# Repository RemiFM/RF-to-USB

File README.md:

# RF-to-USB

 STM32L4-based RF-to-USB dongle using the NRF24 2.4 GHz transceiver. The board includes a USB-A connector on one side and a female SMA antenna connector on the other. It is a 4-layer PCB created using KiCad 9.0 measuring 50 mm x 20 mm.
 
The schematic (PDF) can be found under [documentation/schematic.pdf](documentation/schematic.pdf)  
The manufacturing Gerber files can be found under [hardware/production](hardware/production)
The bill of materials (BOM) can be found under [hardware/RF-to-USB_BOM.csv](hardware/RF-to-USB_BOM.csv) or through the following [Digi-Key list](https://www.digikey.be/en/mylists/list/OKW62PSVJE).
## Acknowledgements

This project is inspired by [STRF-Kicad](https://github.com/pms67/STRF-Kicad) by Philip Salmony, and has been expanded with a 0.91" OLED display and control buttons for additional functionality and monitoring.

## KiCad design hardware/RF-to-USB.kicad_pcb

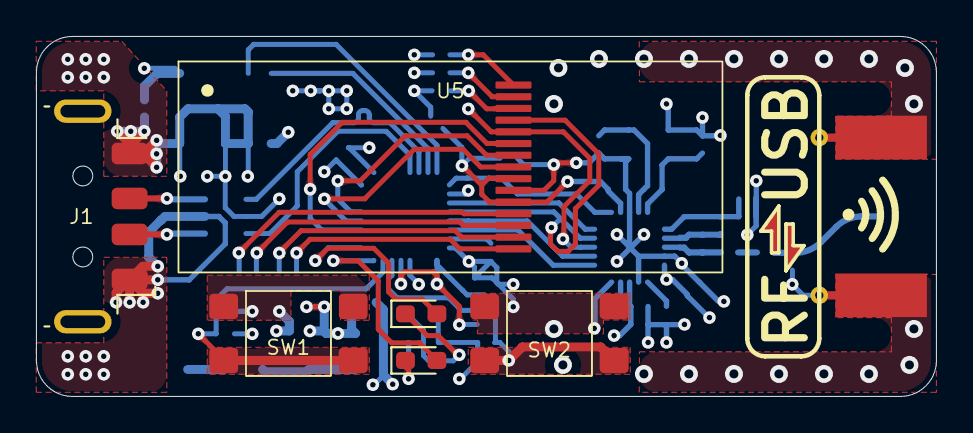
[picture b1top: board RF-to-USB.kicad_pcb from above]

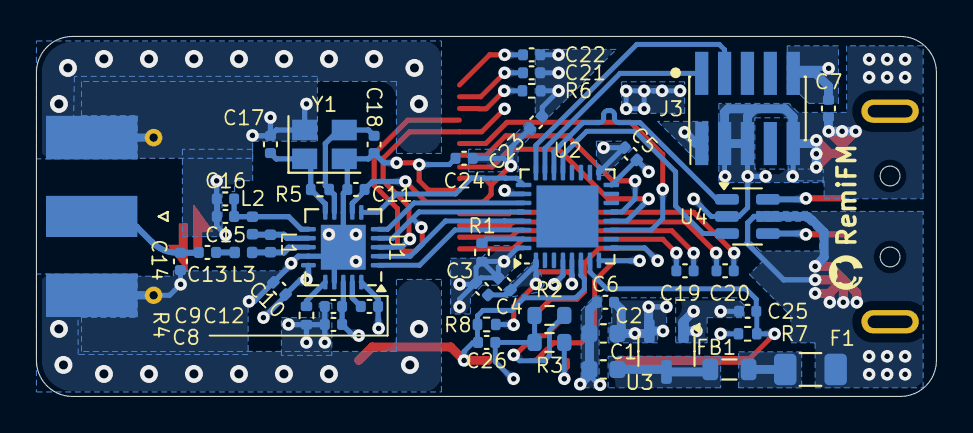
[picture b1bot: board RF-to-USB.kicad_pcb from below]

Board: 4 copper layers, 50.0 x 20.0 mm, 52 parts (46 on the bottom side), 44 nets.

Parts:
C1, C2: 10u; C_0603_1608Metric
C3, C19, C20, C23, C24: 1u; C_0402_1005Metric
C4, C5, C6, C7, C25, C26: 100n; C_0402_1005Metric
C8: 10u; C_0402_1005Metric
C9, C10, C11: 10n; C_0402_1005Metric
C12: 33n; C_0402_1005Metric
C13: 1p5; C_0402_1005Metric
C14: 1p; C_0402_1005Metric
C15: 2n2; C_0402_1005Metric
C16: 4p7; C_0402_1005Metric
C17, C18: 12p; C_0402_1005Metric
C21, C22: 2u2; C_0402_1005Metric
D1: GR; LED_0603_1608Metric_Pad1.05x0.95mm_HandSolder
D2: YE; LED_0603_1608Metric_Pad1.05x0.95mm_HandSolder
F1: 100mA; Fuse_1206_3216Metric
FB1: 100 @ 100MHz; L_0805_2012Metric
J1: USB_A; USB_A_Molex_48037-2200_Horizontal
J2: SMA-F; SMA_Molex_73251-1153_EdgeMount_Horizontal
J3: ARM SWD; PinHeader_2x05_P1.27mm_Vertical_SMD
L1: 8n2; L_0402_1005Metric
L2: 2n7; L_0402_1005Metric
L3: 3n9; L_0402_1005Metric
R1: 10k; R_0402_1005Metric
R2, R3: 2k2; R_0603_1608Metric
R4: 22k; R_0402_1005Metric
R5: 1M; R_0402_1005Metric
R6: 390k; R_0402_1005Metric
R7, R8: 4k7; R_0402_1005Metric
SW1: BTN1; Button_ESwitch_TL3305
SW2: BTN2; Button_ESwitch_TL3305
U1: nRF24L01P; QFN-20-1EP_4x4mm_P0.5mm_EP2.5x2.5mm
U2: STM32L432KBUx; QFN-32-1EP_5x5mm_P0.5mm_EP3.45x3.45mm
U3: XC6206P332MR; SOT-23-3
U4: USBLC6-2SC6; SOT-23-6
U5: OLED Display; Display_Univision_UG-2832HSWEG04
Y1: 16MHz; Crystal_SMD_SeikoEpson_TSX3225-4Pin_3.2x2.5mm

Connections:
+3V3: C2.1, C3.1, C4.1, C5.1, C6.1, C8.1, C9.1, C10.1, C11.1, C23.1, C24.2, J3.1, R7.2, R8.2, U1.7 (VDD), U1.15 (VDD), U1.18 (VDD), U2.1 (VDD), U2.5 (VDDA), U2.17 (VDD), U3.2 (VO), U5.5 (VBAT), U5.7 (VDD)
+5V: F1.1, J1.1 (VBUS), U4.5 (VBUS)
/LED_RX: D1.2 (A), U2.9 (PA3)
/LED_TX: D2.2 (A), U2.8 (PA2)
/NRF_ANT: C13.2, C14.1, J2.1 (In)
/USB_A_D+: J1.3 (D+), U4.6 (I/O1)
/USB_A_D-: J1.2 (D-), U4.4 (I/O2)
BTN1_EXTI: C25.1, R7.1, SW1.1, SW1.2, U2.7 (PA1)
BTN2_EXTI: C26.1, R8.1, SW2.1, SW2.2, U2.6 (PA0)
GND: C1.2, C2.2, C3.2, C4.2, C5.2, C6.2, C7.2, C8.2, C9.2, C10.2, C11.2, C12.2, C14.2, C15.2, C16.2, C17.2, C18.2, C21.2, C22.2, C23.2, C24.1, C25.2, C26.2, J1.4 (GND), J2.2 (Ext), J3.3, J3.5, J3.9, R1.1, R2.1, R3.1, R4.2, R6.1, SW1.3 (K), SW1.4 (A), SW2.3 (K), SW2.4 (A), U1.8 (VSS), U1.14 (VSS), U1.17 (VSS), U1.20 (VSS), U1.21, U2.16 (VSS), U2.32 (VSS), U3.1 (GND), U4.2 (GND), U5.6 (VSS), Y1.2, Y1.4
NRF_ANT1: L1.2, L2.1, U1.12 (ANT1)
NRF_ANT2: L1.1, L3.1, U1.13 (ANT2)
NRF_CE: U1.1 (CE), U2.30 (PB7)
NRF_IRQ: U1.6 (IRQ), U2.25 (PA15)
NRF_VDD_PA: C15.1, C16.1, L2.2, U1.11 (VDD_PA)
NRF_XC1: C17.1, R5.1, U1.10 (XC1), Y1.1
NRF_XC2: C18.1, R5.2, U1.9 (XC2), Y1.3
NRST: C7.1, J3.10, U2.4 (NRST)
unnamed: C13.1, L3.2
unnamed: D1.1 (K), R2.2
unnamed: D2.1 (K), R3.2
unnamed: F1.2, FB1.2
unnamed: C12.1, U1.19 (DVDD)
unnamed: R4.1, U1.16 (IREF)
unnamed: R1.2, U2.31 (PH3)
unnamed: C1.1, FB1.1, U3.3 (VI)
unnamed: C20.2, U5.4 (C1N)
unnamed: C20.1, U5.3 (C1P)
unnamed: C19.2, U5.2 (C2N)
unnamed: C19.1, U5.1 (C2P)
unnamed: R6.2, U5.13 (IREF)
unnamed: C22.1, U5.15 (VCC)
unnamed: C21.1, U5.14 (VCOMH)
OLED_CS: U2.12 (PA6), U5.8 (~CS)
OLED_DC: U2.11 (PA5), U5.10 (D/~C)
OLED_RES: U2.13 (PA7), U5.9 (~RES)
SPI3_MISO: U1.5 (MISO), U2.27 (PB4)
SPI3_MOSI: U1.4 (MOSI), U2.28 (PB5), U5.12 (MOSI)
SPI3_SCK: U1.3 (SCK), U2.26 (PB3), U5.11 (SCLK)
SPI3_~CS: U1.2 (CSN), U2.29 (PB6)
SWCLK: J3.4, U2.24 (PA14)
SWDIO: J3.2, U2.23 (PA13)
USB_D+: U2.22 (PA12), U4.1 (I/O1)
USB_D-: U2.21 (PA11), U4.3 (I/O2)

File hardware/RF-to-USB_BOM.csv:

Reference,Qty,Value,Footprint,Digi-Key,SKU
"C1,C2",2,10u,Capacitor_SMD:C_0603_1608Metric,1276-1038-1-ND,CL10A106KQ8NNNC
"C3,C19,C20,C23,C24",5,1u,Capacitor_SMD:C_0402_1005Metric,1276-1067-1-ND,CL05A105KO5NNNC
"C4,C5,C6,C7,C25,C26",6,100n,Capacitor_SMD:C_0402_1005Metric,1276-1002-1-ND,CL05B104KP5NNNC
C8,1,10u,Capacitor_SMD:C_0402_1005Metric,1276-1451-1-ND,CL05A106MQ5NUNC
"C9,C10,C11",3,10n,Capacitor_SMD:C_0402_1005Metric,1276-1028-1-ND,CL05B103KB5NNNC
C12,1,33n,Capacitor_SMD:C_0402_1005Metric,1276-1177-1-ND,CL05B333KO5NNNC
C13,1,1p5,Capacitor_SMD:C_0402_1005Metric,1276-1656-1-ND,CL05C1R5BB5NNNC
C14,1,1p,Capacitor_SMD:C_0402_1005Metric,1276-1595-1-ND,CL05C010CB5NNNC
C15,1,2n2,Capacitor_SMD:C_0402_1005Metric,1276-1054-1-ND,CL05B222KB5NNNC
C16,1,4p7,Capacitor_SMD:C_0402_1005Metric,1276-6694-1-ND,CL05C4R7CB51PNC
"C17,C18",2,12p,Capacitor_SMD:C_0402_1005Metric,1276-1178-1-ND,CL05C120JB5NNNC
"C21,C22",2,2u2,Capacitor_SMD:C_0402_1005Metric,1276-1461-1-ND,CL05A225KO5NQNC
D1,1,GR,LED_SMD:LED_0603_1608Metric_Pad1.05x0.95mm_HandSolder,732-4971-1-ND,150060GS75000
D2,1,YE,LED_SMD:LED_0603_1608Metric_Pad1.05x0.95mm_HandSolder,732-4981-1-ND,150060YS75000
F1,1,100mA,Fuse:Fuse_1206_3216Metric,F1450CT-ND,0466.125NR
FB1,1,100 @ 100MHz,Inductor_SMD:L_0805_2012Metric,445-MPZ2012S101AT000CT-ND,MPZ2012S101AT000
J1,1,USB_A,RF-to-USB:USB_A_Molex_48037-2200_Horizontal,WM3983CT-ND,480372200
J2,1,SMA-F,Connector_Coaxial:SMA_Molex_73251-1153_EdgeMount_Horizontal,900-0732511153-ND,732511153
J3,1,ARM SWD,Connector_PinHeader_1.27mm:PinHeader_2x05_P1.27mm_Vertical_SMD,1528-2827-ND,4048
L1,1,8n2,Inductor_SMD:L_0402_1005Metric,490-15135-1-ND,LQG15HS8N2H02D
L2,1,2n7,Inductor_SMD:L_0402_1005Metric,490-2615-1-ND,LQG15HS2N7S02D
L3,1,3n9,Inductor_SMD:L_0402_1005Metric,490-2617-1-ND,LQG15HS3N9S02D
R1,1,10k,Resistor_SMD:R_0402_1005Metric,YAG3436CT-ND,AC0402FR-0710KL
"R2,R3",2,2k2,Resistor_SMD:R_0603_1608Metric,13-AC0603FR-7W2K2LCT-ND,AC0603FR-7W2K2L
R4,1,22k,Resistor_SMD:R_0402_1005Metric,13-AC0402FR-1322KLCT-ND,AC0402FR-1322KL
R5,1,1M,Resistor_SMD:R_0402_1005Metric,13-AC0402FR-131MLCT-ND,AC0402FR-131ML
R6,1,390k,Resistor_SMD:R_0402_1005Metric,YAG5736CT-ND,AC0402FR-07390KL
"R7,R8",2,4k7,Resistor_SMD:R_0402_1005Metric,13-AC0402FR-134K7LCT-ND,AC0402FR-134K7L
SW1,1,BTN1,RF-to-USB:Button_ESwitch_TL3305,EG5353CT-ND,TL3305AF260QG
SW2,1,BTN2,RF-to-USB:Button_ESwitch_TL3305,EG5353CT-ND,TL3305AF260QG
U1,1,nRF24L01P,Package_DFN_QFN:QFN-20-1EP_4x4mm_P0.5mm_EP2.5x2.5mm,4823-NRF24L01P-R7CT-ND,NRF24L01P-R7
U2,1,STM32L432KBUx,Package_DFN_QFN:QFN-32-1EP_5x5mm_P0.5mm_EP3.45x3.45mm,497-16577-ND,STM32L432KBU6
U3,1,XC6206P332MR,Package_TO_SOT_SMD:SOT-23-3,893-XC6206P332MR-GCT-ND,XC6206P332MR-G
U4,1,USBLC6-2SC6,Package_TO_SOT_SMD:SOT-23-6,497-5235-1-ND,USBLC6-2SC6
U5,1,OLED Display,RF-to-USB:Display_Univision_UG-2832HSWEG04,1568-LCD-24177-ND,LCD-24177
Y1,1,16MHz,Crystal:Crystal_SMD_SeikoEpson_TSX3225-4Pin_3.2x2.5mm,SER4069CT-ND,TSX-3225 16.0000MF09Z-AC0
extra,1,SWD alternative,None,S9012E-05-ND,GRPB052VWQS-RC

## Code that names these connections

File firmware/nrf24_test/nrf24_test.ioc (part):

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Mcu.Name=STM32L432K(B-C)Ux
Mcu.Package=UFQFPN32
Mcu.UserName=STM32L432KBUx
PA0.GPIOParameters=GPIO_Label
PA0.GPIO_Label=BTN2_EXTI
PA0.Signal=GPXTI0
PA1.GPIOParameters=GPIO_Label
PA1.GPIO_Label=BTN1_EXTI
PA1.Signal=GPXTI1
PA11.Mode=Device
PA11.Signal=USB_DM
PA12.Mode=Device
PA12.Signal=USB_DP
PA13\ (JTMS-SWDIO).Mode=Serial_Wire
PA13\ (JTMS-SWDIO).Signal=SYS_JTMS-SWDIO
PA14\ (JTCK-SWCLK).Mode=Serial_Wire
PA14\ (JTCK-SWCLK).Signal=SYS_JTCK-SWCLK
PA15\ (JTDI).GPIOParameters=GPIO_Label
PA15\ (JTDI).GPIO_Label=NRF_IRQ
PA15\ (JTDI).Signal=GPXTI15
PA2.GPIOParameters=GPIO_Label
PA2.GPIO_Label=LED_TX
PA2.Signal=GPIO_Output
PA3.GPIOParameters=GPIO_Label
PA3.GPIO_Label=LED_RX
PA3.Signal=GPIO_Output
PA5.GPIOParameters=GPIO_Label
PA5.GPIO_Label=OLED_DC
PA5.Signal=GPIO_Output
PA6.GPIOParameters=GPIO_Label
PA6.GPIO_Label=OLED_CS
PA6.Signal=GPIO_Output
PA7.GPIOParameters=GPIO_Label
PA7.GPIO_Label=OLED_RES
PA7.Signal=GPIO_Output
PB3\ (JTDO-TRACESWO).Mode=Full_Duplex_Master
PB3\ (JTDO-TRACESWO).Signal=SPI3_SCK
PB4\ (NJTRST).Mode=Full_Duplex_Master
PB4\ (NJTRST).Signal=SPI3_MISO
PB5.Mode=Full_Duplex_Master
PB5.Signal=SPI3_MOSI
PB6.GPIOParameters=PinState,GPIO_Label
PB6.GPIO_Label=SPI3_CS
PB6.PinState=GPIO_PIN_SET
PB6.Signal=GPIO_Output
PB7.GPIOParameters=GPIO_Label
PB7.GPIO_Label=NRF_CE
PB7.Signal=GPIO_Output
RCC.HSE_VALUE=8000000
RCC.SYSCLKFreq_VALUE=80000000
RCC.SYSCLKSource=RCC_SYSCLKSOURCE_PLLCLK
board=custom

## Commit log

2025-03-11 NRF24 transceiver schematic
2025-03-11 display footprint
2025-03-17 OLED footprint & schematic
2025-03-17 component placement
2025-04-03 routing updates
2025-04-07 routing updates
    all DRC errors & warnings resolved
2025-04-08 silkscreen adjustments
2025-04-09 readme & documentation
2025-04-09 BOM updates
2025-04-29 OLED driver
2025-05-15 NRF24 firmware fixes
    Troubleshooting issues, SPI clock speed was set too high for the NRF chip and had to be reduced (40MHz -> 5MHz)
2025-05-25 I/O interrupt routines
2025-05-26 state machine
2025-07-30 MCU pin definitions
2026-03-24 transmitter mode fixes
2026-03-24 USB Communication (CDC)
